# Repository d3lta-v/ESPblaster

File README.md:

# ESPblaster

Designed by [FourierIndustries](https://fourier.industries) by Pan Ziyue

## Overview
The ESPblaster is a simple and straightforward ESP8266-01 flashing device, with onboard logic level translation, high stability voltage regulation, and an active-low DIP switch to toggle the ESP8266-01 module's startup states. All of the components are either through-hole or 1206 SMD, which makes the board easily solderable. JP1, JP2 and JP3 are jumpers on the board that should be closed by default with a solder blob. This circuit board provides a quick and easy alternative to flashing or interacting with the ESP8266-01 module without complicated breadboarding. 

## Interface
The ESPblaster has a 6-pin serial interface:

* **DTR** (not wired to anything)
* **TXO** (Transmit Out) [5V compliant]
* **RXI** (Receive In) [5V compliant]
* **VCC** (5V in)
* **GND**
* **RX3** (Receive In) [3.3V compliant]

## DIP switches
The ESPblaster packs a DIP switch to alter the startup states, as well as reset the module or disable the module. 

#### Warning: the DIP switch is an active low switch! This means that flipping the switch up to "On" will pull low the circuit!

The DIP switches are responsible for the following states (from left to right, from the front face of the board):

1. **CH_PD** (Chip Enable)
2. **RST** (Reset)
3. **GPIO0**
4. **GPIO2**

## Startup states table

|                  | CH_PD | RST | GPIO0 | GPIO2 |
|------------------|:-----:|:---:|:-----:|:-----:|
| Normal Startup   |   1   |  1  |   1   |   1   |
| Flash bootloader |   1   |  1  |   0   |   1   |
| Reset            |   1   |  0  |   X   |   X   |
| Disable          |   0   |  X  |   X   |   X   |

## Solder blob jumpers
JP1, JP2 and JP3 are solder blob jumpers, which should be closed by default. They are responsible for the following:

* **JP1**: Connects GPIO0 to the DIP switch
* **JP2**: Connects GPIO2 to the DIP switch
* **JP3**: When connected, the RXI signal will pass through the logic level shifter and if disconnected, you must use the RX3 pin to supply 3.3V logic for the RX of the ESP8266-01.

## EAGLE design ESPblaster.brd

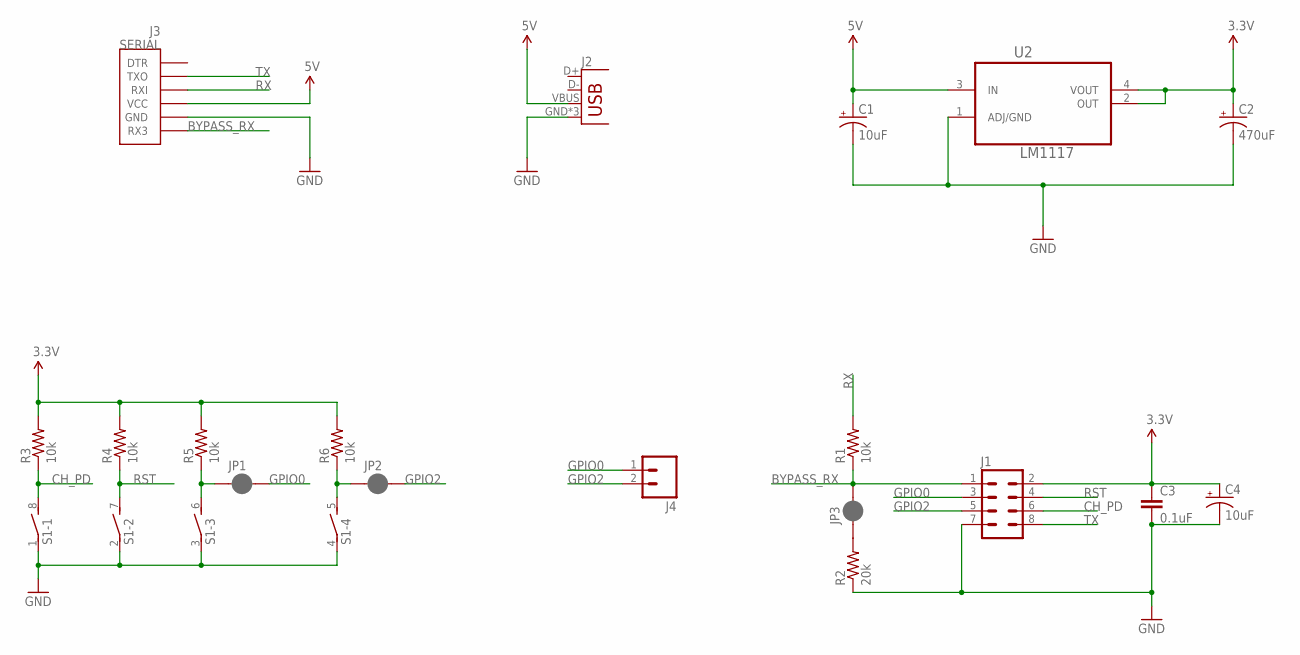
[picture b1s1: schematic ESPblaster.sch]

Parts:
C1, C4: 10uF; EIA3216-KIT
C2: 470uF; CPOL-RADIAL-100UF-25V
C3: 0.1uF; 1206
J1: M04X2; 2X4
J2: USB-MICROB
J3: SERIAL; CP2102_DEVICE_SIDE_ESP8266
J4: M02LOCK; 1X02_LOCK
JP1, JP2, JP3: JUMPER-PAD-2-NC_BY_PASTEFULL-BOX-SILK; PAD-JUMPER-2-NC_BY_PASTE_YES_SILK_FULL_BOX
R1, R3, R4, R5, R6: 10k; 1206
R2: 20k; 1206
S1: DIP04S
U2: LM1117; SOT230P696X180-4N

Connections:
3.3V: C2.1 (+), C3.1, C4.A (+), J1.2, R3.2, R4.2, R5.2, R6.2, U2.2 (OUT), U2.4 (VOUT)
5V: C1.A (+), J2.VBUS, J3.P$4 (VCC), U2.3 (IN)
BYPASS_RX: J1.1, J3.P$6 (RX3), JP3.2, R1.1
CH_PD: J1.6, R3.1, S1.8 (2)
GND: C1.C (-), C2.2 (-), C3.2, C4.C (-), J1.7, J2.GND, J2.MT1 (GND), J2.MT2 (GND), J3.P$5 (GND), R2.1, S1.1, S1.2 (1), S1.3 (1), S1.4 (1), U2.1 (ADJ/GND)
GPIO0: J1.3, J4.1, JP1.2
GPIO2: J1.5, J4.2, JP2.2
unnamed: JP3.1, R2.2
unnamed: JP2.1, R6.1, S1.5 (2)
unnamed: JP1.1, R5.1, S1.6 (2)
RST: J1.4, R4.1, S1.7 (2)
RX: J3.P$3 (RXI), R1.2
TX: J1.8, J3.P$2 (TXO)

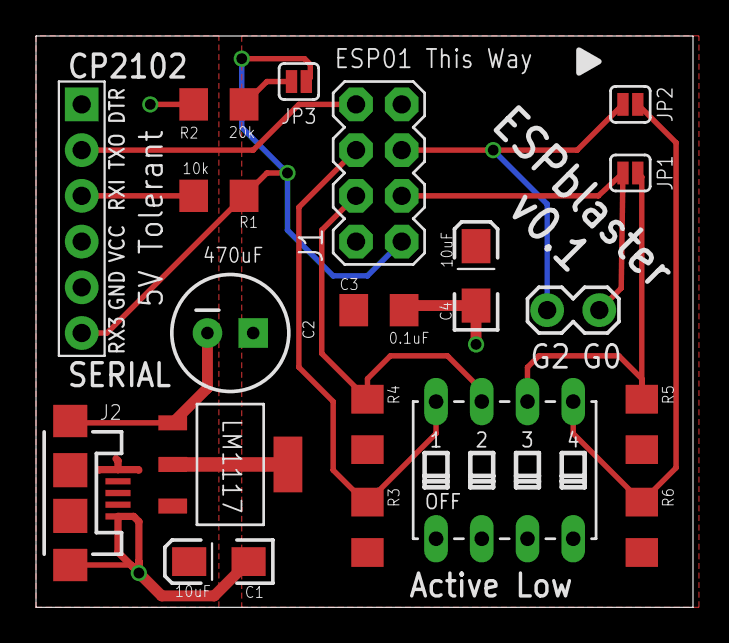
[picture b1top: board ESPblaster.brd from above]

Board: 2 copper layers, 36.5 x 31.7 mm, 20 parts (0 on the bottom side), 13 nets.

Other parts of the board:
U$1: FOURIERINDUSTRIES-SMALL-INV

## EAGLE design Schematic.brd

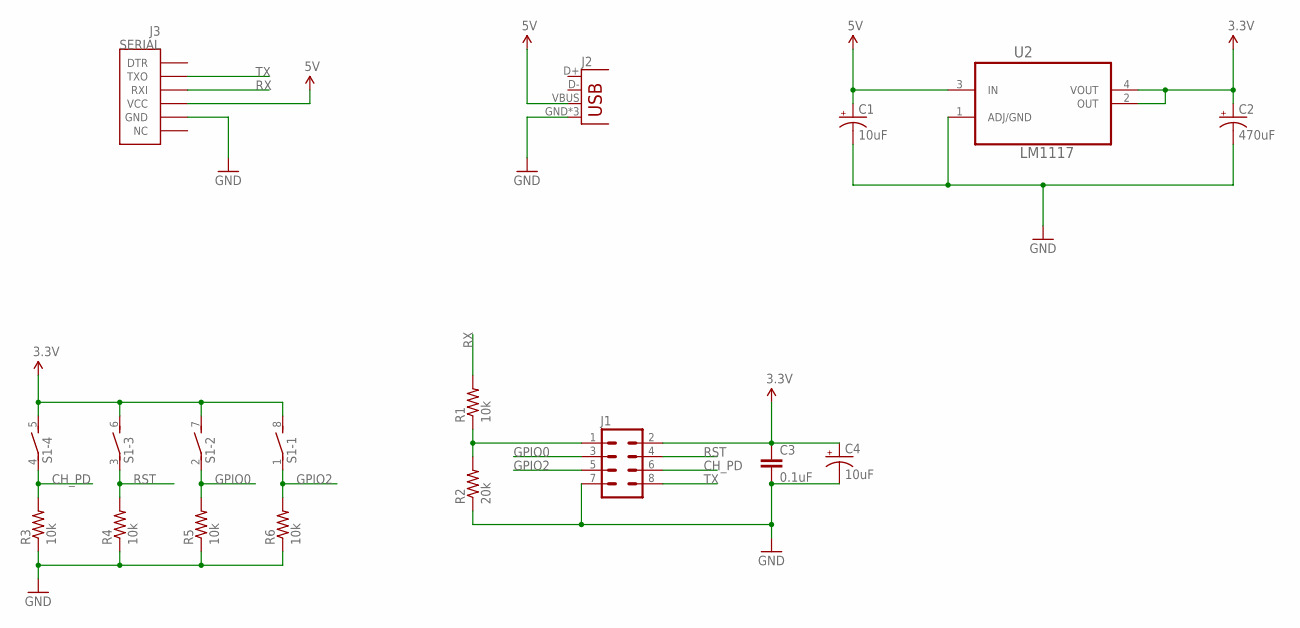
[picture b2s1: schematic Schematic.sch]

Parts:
C1, C4: 10uF; EIA3216-KIT
C2: 470uF; CPOL-RADIAL-100UF-25V
C3: 0.1uF; 1206
J1: M04X2; 2X4
J2: USB-MICROB
J3: SERIAL; CP2102_DEVICE_SIDE
R1, R3, R4, R5, R6: 10k; 1206
R2: 20k; 1206
S1: DIP04S
U2: LM1117; SOT230P696X180-4N

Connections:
3.3V: C2.1 (+), C3.1, C4.A (+), J1.2, S1.5 (2), S1.6 (2), S1.7 (2), S1.8 (2), U2.2 (OUT), U2.4 (VOUT)
5V: C1.A (+), J2.VBUS, J3.P$4 (VCC), U2.3 (IN)
CH_PD: J1.6, R3.2, S1.4 (1)
GND: C1.C (-), C2.2 (-), C3.2, C4.C (-), J1.7, J2.GND, J2.MT1 (GND), J2.MT2 (GND), J3.P$5 (GND), R2.1, R3.1, R4.1, R5.1, R6.1, U2.1 (ADJ/GND)
GPIO0: J1.3, R5.2, S1.2 (1)
GPIO2: J1.5, R6.2, S1.1
unnamed: J1.1, R1.1, R2.2
RST: J1.4, R4.2, S1.3 (1)
RX: J3.P$3 (RXI), R1.2
TX: J1.8, J3.P$2 (TXO)

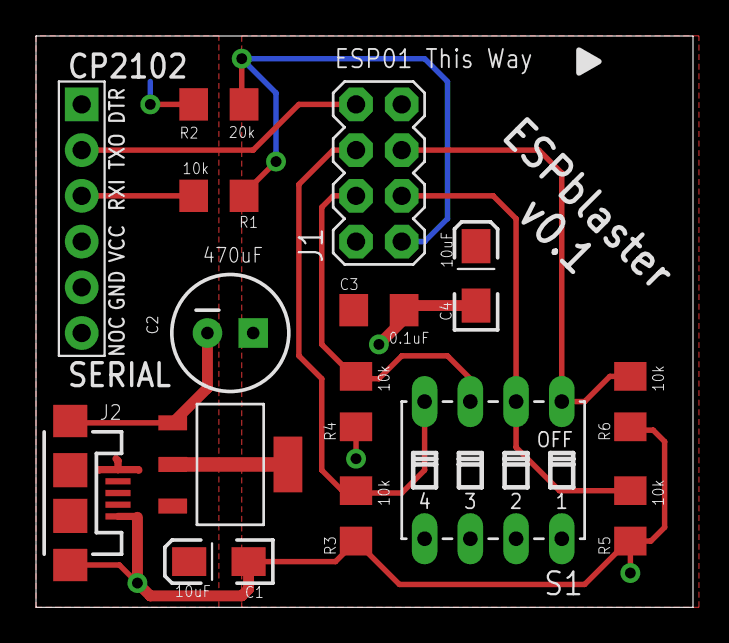
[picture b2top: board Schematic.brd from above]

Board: 2 copper layers, 36.5 x 31.7 mm, 16 parts (0 on the bottom side), 10 nets.

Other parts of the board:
U$1: FOURIERINDUSTRIES-SMALL-INV

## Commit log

2017-03-05 Added some styling
2017-03-05 Cleaned up text positions
2017-03-05 Reorganised folders
2017-03-06 Redesigned switches to pull HIGH, added truth table, cuttable jumper for G2 and G0
2017-03-06 Removed temp Mac file
2017-03-06 Added logic high and low silkscreen
2017-03-06 Fixed orientation of DIP switch
2017-03-06 final edits
2017-04-29 Rearranged files and added image preview
2017-04-29 Added README

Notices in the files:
parts and their libraries:
SparkFun-Capacitors: Licensing: Creative Commons ShareAlike 4.0 International - https://creativecommons.org/licenses/by-sa/4.0
